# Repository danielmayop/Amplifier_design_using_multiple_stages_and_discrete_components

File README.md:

# Amplificador multietapa con componentes discretos

Laboratorio 8 de *Análisis y Diseño de Circuitos Analógicos I*: diseño e implementación de un amplificador clase A de varias etapas, usando solo componentes discretos (sin circuitos integrados).

El enunciado completo está en [`Laboratorio8.pdf`](Laboratorio8.pdf).

## Especificaciones

- Ganancia de tensión mayor a 300.
- Excursión de ±5 V sobre una resistencia de 470 Ω con acople capacitivo.
- Impedancia de entrada mayor a 300 kΩ.
- Impedancia de salida menor a 200 Ω.
- Debe trabajar en el rango de frecuencias de 100 Hz a 50 kHz.
- Consumo de potencia media total de 240 mW o menos.

Observaciones principales del enunciado: la fuente de tensión debe ser del menor valor posible y no superar los 20 V, y la impedancia de salida del generador es de 50 Ω. El resto de las observaciones están en el PDF.

## Etapas del amplificador

El amplificador se compone de cuatro etapas en cascada, más una fuente de corriente en la parte inferior del circuito.

| Etapa | Configuración | Para qué sirve |
|-------|---------------|----------------|
| 1 | JFET (`J3`, LS844) | Lograr una impedancia de entrada grande. |
| 2 | Emisor común con capacitor en el emisor (`Q11`) | Dar la mayor parte de la ganancia: el capacitor puentea la resistencia de emisor y permite amplificar una cantidad grande. |
| 3 | Emisor común sin capacitor en el emisor (`Q10`) | Amplificar un poco más la señal. |
| 4 | Colector común (`Q8`) | Lograr la impedancia de salida baja que pide la especificación. |
| — | Fuente de corriente (`Q9`) | Está conectada al emisor del colector común y fija su corriente de polarización. |

Los transistores bipolares son 2N3904. Los nombres de los componentes corresponden al esquemático de LTspice `Clase_A.asc`, que se alimenta con 15 V.

## Contenido del repositorio

- [`Multietapa/Kicad Multietapa/`](Multietapa/Kicad%20Multietapa/): proyecto de KiCad con el esquemático y el diseño del PCB (incluye backups automáticos en `.zip`).
- [`Multietapa/LTSpice Multietapa/`](Multietapa/LTSpice%20Multietapa/): simulaciones en LTspice (`Clase_A.asc`, `Draft1` y `Draft2`) con sus archivos de resultados `.log` y `.raw`.
- [`Laboratorio8.pdf`](Laboratorio8.pdf): enunciado y especificaciones.
- `Multietapa_pcb1.jpg`, `Multietapa_pcb2.jpg` y `Multietapa_pcb3.jpg`: imágenes del PCB.

## Imágenes del PCB

## Cómo abrir los archivos

- Los archivos `.asc` se abren con [LTspice](https://www.analog.com/en/resources/design-tools-and-calculators/ltspice-simulator.html).
- El proyecto de KiCad se abre desde [KiCad](https://www.kicad.org/) con el archivo `Multietapa.kicad_pro`.

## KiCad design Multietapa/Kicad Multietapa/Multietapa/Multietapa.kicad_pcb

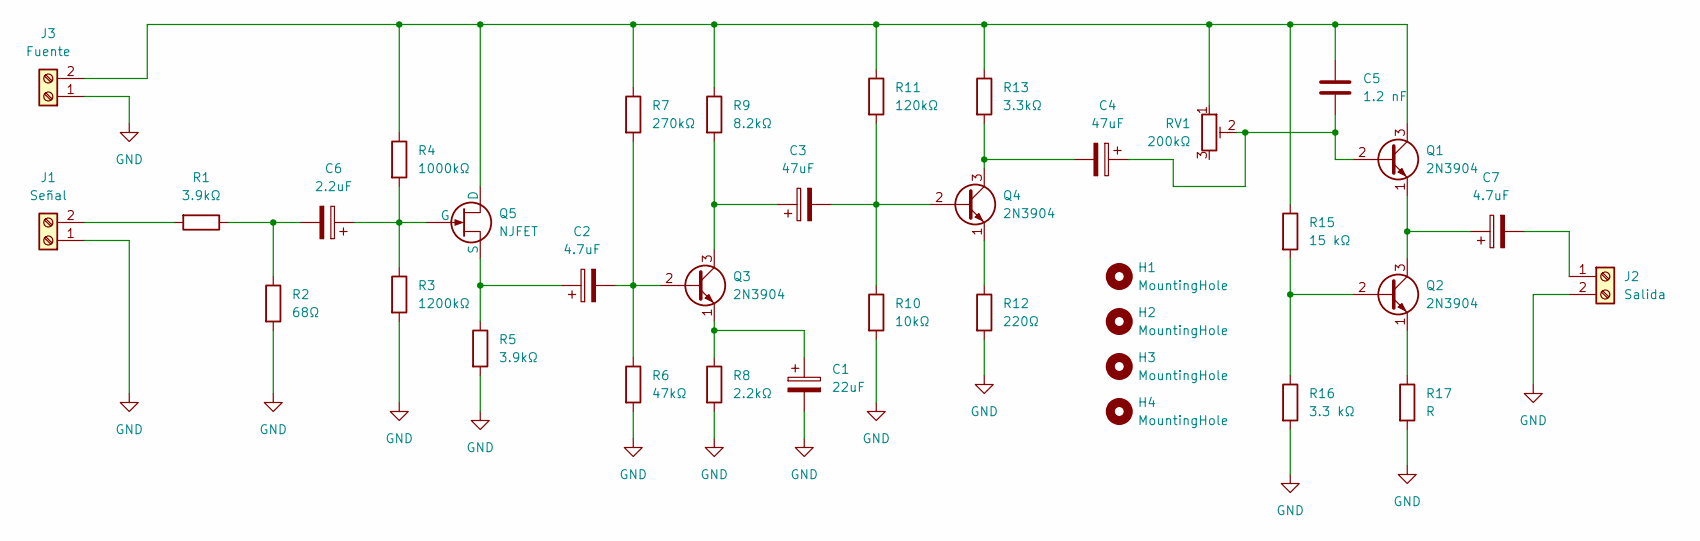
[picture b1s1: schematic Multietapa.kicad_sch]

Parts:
C1: 22uF; CP_Radial_D5.0mm_P2.00mm
C2, C7: 4.7uF; CP_Radial_D5.0mm_P2.00mm
C3, C4: 47uF; CP_Radial_D6.3mm_P2.50mm
C5: 1.2 nF; C_Disc_D3.0mm_W1.6mm_P2.50mm
C6: 2.2uF; CP_Radial_D5.0mm_P2.00mm
H1, H2, H3, H4: MountingHole; MountingHole_3.2mm_M3
J1: Señal; TerminalBlock_Phoenix_MKDS-1,5-2_1x02_P5.00mm_Horizontal
J2: Salida; TerminalBlock_Phoenix_MKDS-1,5-2_1x02_P5.00mm_Horizontal
J3: Fuente; TerminalBlock_Phoenix_MKDS-1,5-2_1x02_P5.00mm_Horizontal
Q1, Q2, Q3, Q4: 2N3904; TO-92_Inline
Q5: NJFET; TO-92_Inline
R1, R5: 3.9kΩ; R_Axial_DIN0207_L6.3mm_D2.5mm_P7.62mm_Horizontal
R2: 68Ω; R_Axial_DIN0207_L6.3mm_D2.5mm_P7.62mm_Horizontal
R3: 1200kΩ; R_Axial_DIN0207_L6.3mm_D2.5mm_P7.62mm_Horizontal
R4: 1000kΩ; R_Axial_DIN0207_L6.3mm_D2.5mm_P7.62mm_Horizontal
R6: 47kΩ; R_Axial_DIN0207_L6.3mm_D2.5mm_P7.62mm_Horizontal
R7: 270kΩ; R_Axial_DIN0207_L6.3mm_D2.5mm_P7.62mm_Horizontal
R8: 2.2kΩ; R_Axial_DIN0207_L6.3mm_D2.5mm_P7.62mm_Horizontal
R9: 8.2kΩ; R_Axial_DIN0207_L6.3mm_D2.5mm_P7.62mm_Horizontal
R10: 10kΩ; R_Axial_DIN0207_L6.3mm_D2.5mm_P7.62mm_Horizontal
R11: 120kΩ; R_Axial_DIN0207_L6.3mm_D2.5mm_P7.62mm_Horizontal
R12: 220Ω; R_Axial_DIN0207_L6.3mm_D2.5mm_P7.62mm_Horizontal
R13: 3.3kΩ; R_Axial_DIN0207_L6.3mm_D2.5mm_P7.62mm_Horizontal
R15: 15 kΩ; R_Axial_DIN0207_L6.3mm_D2.5mm_P7.62mm_Horizontal
R16: 3.3 kΩ; R_Axial_DIN0207_L6.3mm_D2.5mm_P7.62mm_Horizontal
R17: R; R_Axial_DIN0207_L6.3mm_D2.5mm_P7.62mm_Horizontal
RV1: 200kΩ; Potentiometer_Bourns_3296W_Vertical

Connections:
GND: C1.2, J1.1, J2.2, J3.1, R2.2, R3.2, R5.2, R6.2, R8.2, R10.2, R12.2, R16.2, R17.2
unnamed: C6.2, R1.1, R2.1
unnamed: J1.2, R1.2
unnamed: C7.2, J2.1
unnamed: C5.1, J3.2, Q1.3 (C), Q5.1 (D), R4.1, R7.1, R9.1, R11.1, R13.1, R15.1, RV1.1
unnamed: C4.1, C5.2, Q1.2 (B), RV1.2
unnamed: C7.1, Q1.1 (E), Q2.3 (C)
unnamed: Q2.2 (B), R15.2, R16.1
unnamed: Q2.1 (E), R17.1
unnamed: C2.2, Q3.2 (B), R6.1, R7.2
unnamed: C3.1, Q3.3 (C), R9.2
unnamed: C1.1, Q3.1 (E), R8.1
unnamed: C3.2, Q4.2 (B), R10.1, R11.2
unnamed: C4.2, Q4.3 (C), R13.2
unnamed: Q4.1 (E), R12.1
unnamed: C6.1, Q5.2 (G), R3.1, R4.2
unnamed: C2.1, Q5.3 (S), R5.1

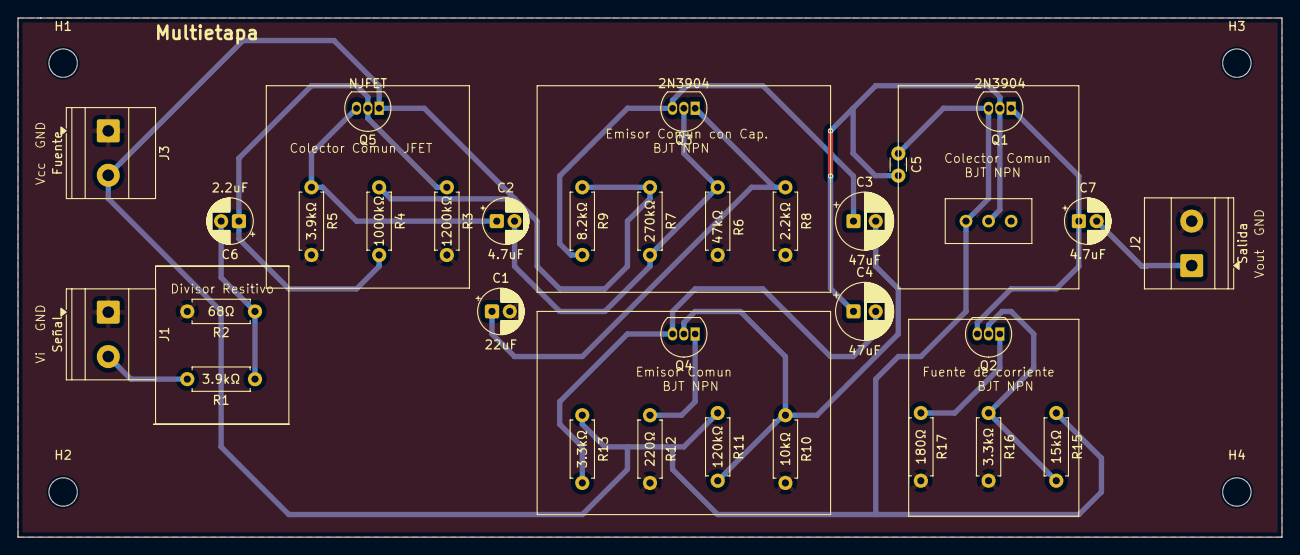
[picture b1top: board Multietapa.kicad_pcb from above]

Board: 2 copper layers, 142.2 x 58.4 mm, 36 parts (0 on the bottom side), 17 nets.
